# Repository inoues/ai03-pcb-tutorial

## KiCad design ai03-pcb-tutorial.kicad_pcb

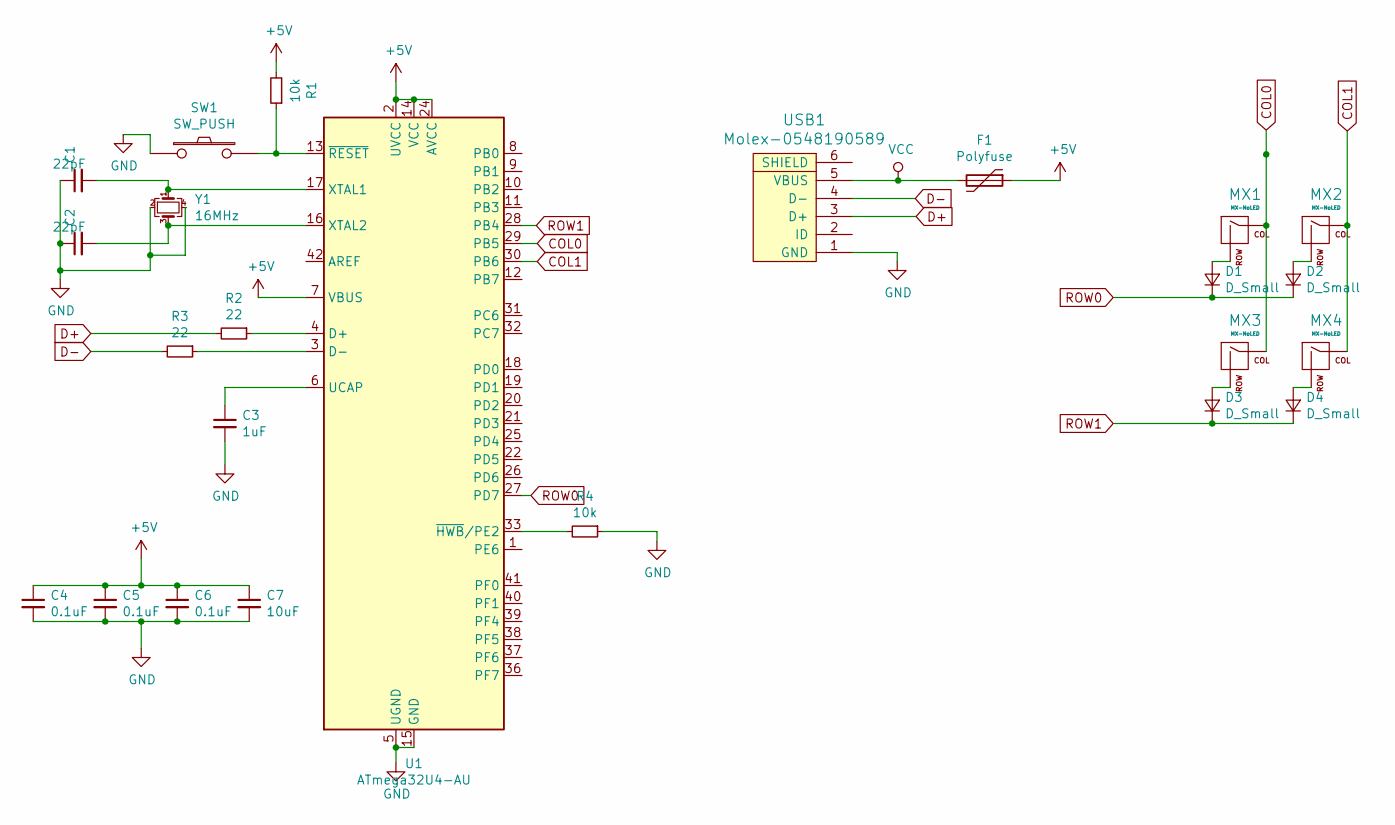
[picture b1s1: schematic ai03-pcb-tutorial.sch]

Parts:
C1, C2: 22pF; C_0805_2012Metric_Pad1.15x1.40mm_HandSolder
C3: 1uF; C_0805_2012Metric_Pad1.15x1.40mm_HandSolder
C4, C5, C6: 0.1uF; C_0805_2012Metric_Pad1.15x1.40mm_HandSolder
C7: 10uF; C_0805_2012Metric_Pad1.15x1.40mm_HandSolder
D1, D2, D3, D4: D_Small; D_SOD-123
F1: Polyfuse; Fuse_1206_3216Metric_Pad1.42x1.75mm_HandSolder
MX1, MX2, MX3, MX4: MX-NoLED; MX-1U-NoLED
R1, R4: 10k; R_0805
R2, R3: 22; R_0805
SW1: SW_PUSH; SKQG-1155865
U1: ATmega32U4-AU; TQFP-44_10x10mm_P0.8mm
USB1: Molex-0548190589
Y1: 16MHz; Crystal_SMD_3225-4Pin_3.2x2.5mm_HandSoldering

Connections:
+5V: C4.1, C5.1, C6.1, C7.1, F1.1, R1.2, U1.2 (UVCC), U1.7 (VBUS), U1.14 (VCC), U1.24 (AVCC), U1.34 (VCC), U1.44 (AVCC)
COL0: MX1.1 (COL), MX3.1 (COL), U1.29 (PB5)
COL1: MX2.1 (COL), MX4.1 (COL), U1.30 (PB6)
D+: R2.2, USB1.3 (D+)
D-: R3.2, USB1.4 (D-)
GND: C1.1, C2.1, C3.2, C4.2, C5.2, C6.2, C7.2, R4.1, SW1.1, U1.5 (UGND), U1.15 (GND), U1.23 (GND), U1.35 (GND), U1.43 (GND), USB1.1 (GND), Y1.2, Y1.4
unnamed: C1.2, U1.17 (XTAL1), Y1.1
unnamed: C2.2, U1.16 (XTAL2), Y1.3
unnamed: C3.1, U1.6 (UCAP)
unnamed: D1.2 (A), MX1.2 (ROW)
unnamed: D2.2 (A), MX2.2 (ROW)
unnamed: D3.2 (A), MX3.2 (ROW)
unnamed: D4.2 (A), MX4.2 (ROW)
unnamed: R1.1, SW1.2, U1.13 (~RESET)
unnamed: R2.1, U1.4 (D+)
unnamed: R3.1, U1.3 (D-)
unnamed: R4.2, U1.33 (~HWB~/PE2)
ROW0: D1.1 (K), D2.1 (K), U1.27 (PD7)
ROW1: D3.1 (K), D4.1 (K), U1.28 (PB4)
VCC: F1.2, USB1.5 (VBUS)

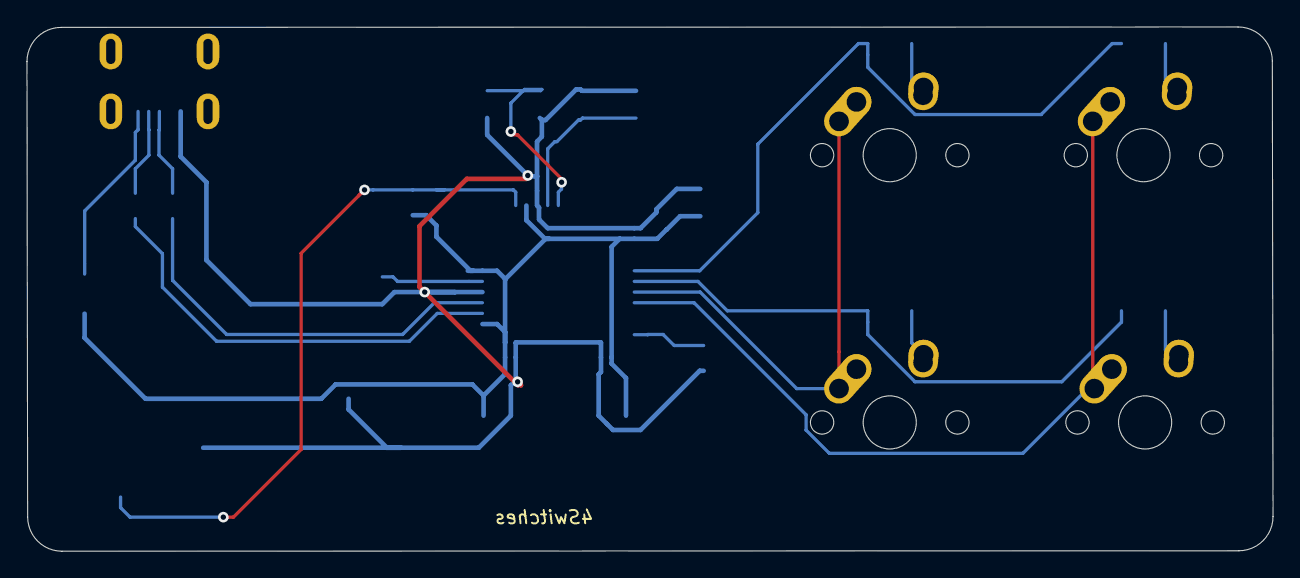
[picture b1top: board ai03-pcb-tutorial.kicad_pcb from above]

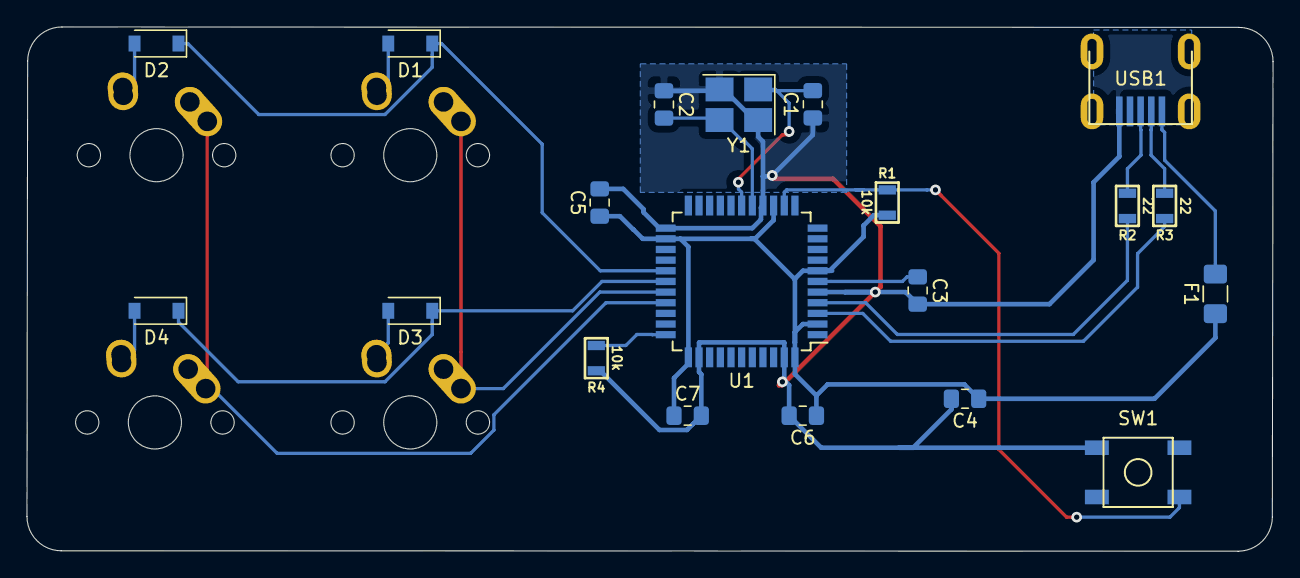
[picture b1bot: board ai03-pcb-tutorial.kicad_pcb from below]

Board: 2 copper layers, 93.6 x 39.4 mm, 24 parts (20 on the bottom side), 20 nets.

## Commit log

2019-11-03 create new project
2019-11-03 add submodueles
2019-11-03 setting raibraries
2019-11-03 add Resister
2019-11-03 save sch
2019-11-04 set reset switch, crystal
2019-11-05 set Footprints
2019-11-05 pcb set init
2019-11-10 chenge footprint R
2019-11-10 set components position
2019-11-10 draw edge line
2019-11-13 first try Routing
2019-11-26 reseet routing
2019-11-26 re routing
2019-11-28 adjust routeing
2019-12-22 reset edge line
    reset edge line
2019-12-30 Ground fills
